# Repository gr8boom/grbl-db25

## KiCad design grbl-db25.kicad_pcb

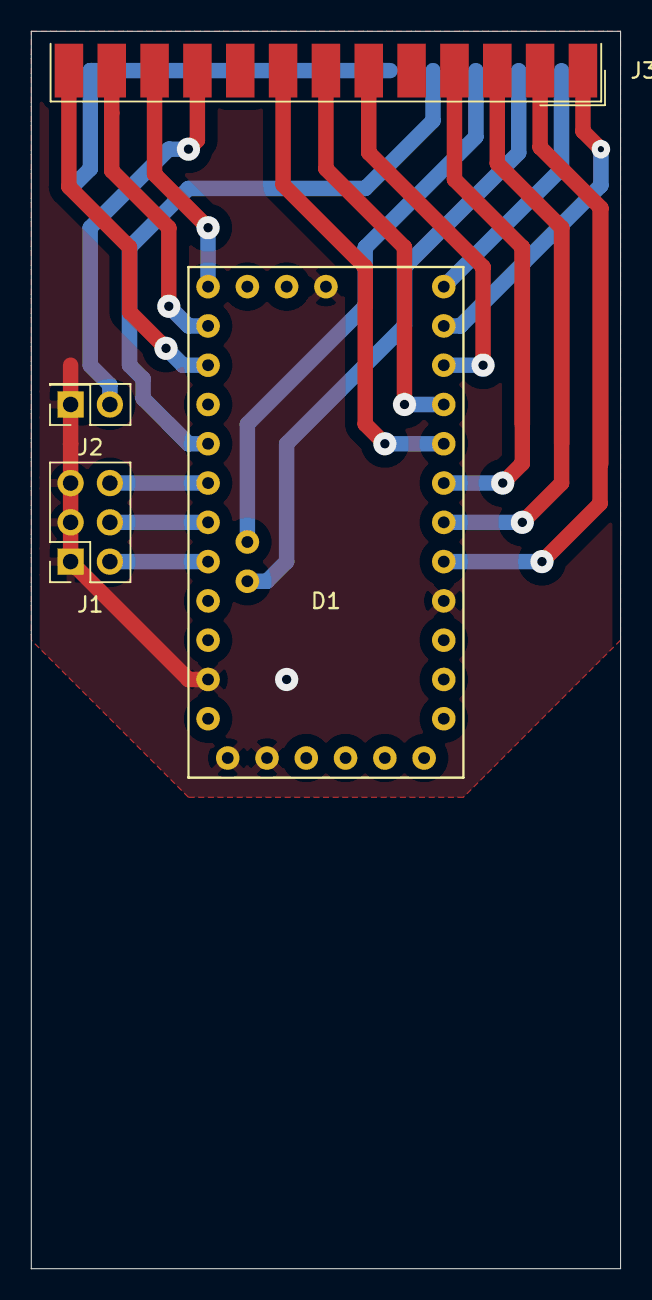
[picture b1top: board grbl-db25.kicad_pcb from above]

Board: 2 copper layers, 38.1 x 80.0 mm, 4 parts (0 on the bottom side), 19 nets.

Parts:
D1: ProMini
J1: Conn_02x03_Odd_Even; PinSocket_2x03_P2.54mm_Vertical
J2: Conn_02x01; PinSocket_2x01_P2.54mm_Vertical
J3: DB25_Male; DSUB-25_Male_EdgeMount_P2.77mm

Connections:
DIR1X: D1.7, J3.6
DIR2Y: D1.6, J3.7
DIR3Z: D1.5, J3.8
ENABLE: D1.8, J3.1
GND: D1.G, J1.1, J1.3, J1.5, J2.1, J3.18, J3.19, J3.20, J3.21, J3.22, J3.23, J3.24, J3.25
HOLD: D1.A2, J1.4
IN1-ESTOP: J2.2, J3.10
IN2X: D1.10, J3.11
IN3Y: D1.11, J3.12
IN4Z: D1.12, J3.13
IN5PROBE: D1.A5, J3.15
PWM: D1.9, J3.14
RELAY1FLOOD: D1.A4, J3.16
RELAY2MIST: D1.A0, J3.17
START: D1.A3, J1.2
STEP1X: D1.2, J3.2
STEP2Y: D1.3, J3.3
STEP3Z: D1.4, J3.4
STOP: D1.A1, J1.6

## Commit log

2021-03-12 Added gitignore
2021-03-13 base cheme but need wire some pins
2021-03-17 one side soldering
